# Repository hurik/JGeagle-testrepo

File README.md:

Check [visual-diffs-for-eagle-and-git](https://github.com/hurik/visual-diffs-for-eagle-and-git) for more information!

Using [9 Degrees of Freedom - Razor IMU](http://www.sparkfun.com/products/10736) and [Triple Axis Accelerometer & Gyro Breakout - MPU-6050](http://www.sparkfun.com/products/11028) eagle files from [SparkFun Electronics](http://www.sparkfun.com/).

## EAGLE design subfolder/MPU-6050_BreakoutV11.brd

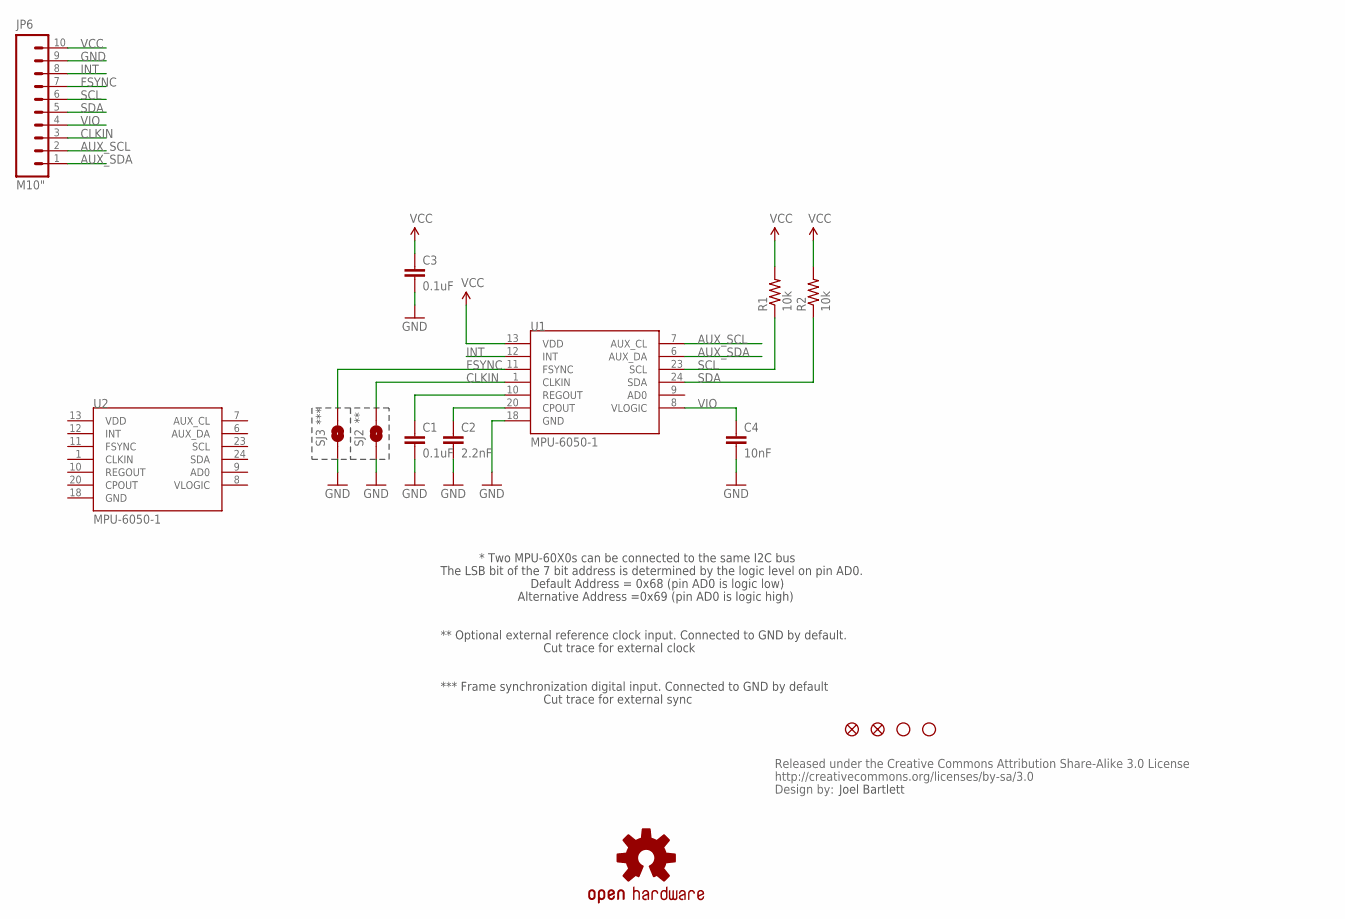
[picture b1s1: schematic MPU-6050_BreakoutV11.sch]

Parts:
C1, C3: 0.1uF; 0402-CAP
C2: 2.2nF; 0402-CAP
C4: 10nF; 0402-CAP
JP2, JP5: FIDUCIALUFIDUCIAL; MICRO-FIDUCIAL
JP3, JP4: STAND-OFFTIGHT; STAND-OFF-TIGHT
JP6: M10"; 1X10
R1, R2: 10k; 0402-RES
SJ2, SJ3: SOLDERJUMPERTRACE; SJ_2S-TRACE
U1, U2: MPU-6050-1; QFN-24-4MM2
U3: CREATIVE_COMMONS
U$1: OSHW-LOGOS; OSHW-LOGO-S

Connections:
AUX_SCL: JP6.2, U1.7 (AUX_CL)
AUX_SDA: JP6.1, U1.6 (AUX_DA)
CLKIN: JP6.3, SJ2.2, U1.1 (CLKIN)
FSYNC: JP6.7, SJ3.2, U1.11 (FSYNC)
GND: C1.2, C2.2, C3.2, C4.2, JP6.9, SJ2.1, SJ3.1, U1.18 (GND)
INT: JP6.8, U1.12 (INT)
unnamed: C2.1, U1.20 (CPOUT)
unnamed: C1.1, U1.10 (REGOUT)
SCL: JP6.6, R1.1, U1.23 (SCL)
SDA: JP6.5, R2.1, U1.24 (SDA)
VCC: C3.1, JP6.10, R1.2, R2.2, U1.13 (VDD)
VIO: C4.1, JP6.4, U1.8 (VLOGIC)

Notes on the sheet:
Joel Bartlett
*** Frame synchronization digital input. Connected to GND by default
***
Cut trace for external sync
* Two MPU-60X0s can be connected to the same I2C bus
Default Address = 0x68 (pin AD0 is logic low)
Alternative Address =0x69 (pin AD0 is logic high)
The LSB bit of the 7 bit address is determined by the logic level on pin AD0.
** Optional external reference clock input. Connected to GND by default.
Cut trace for external clock

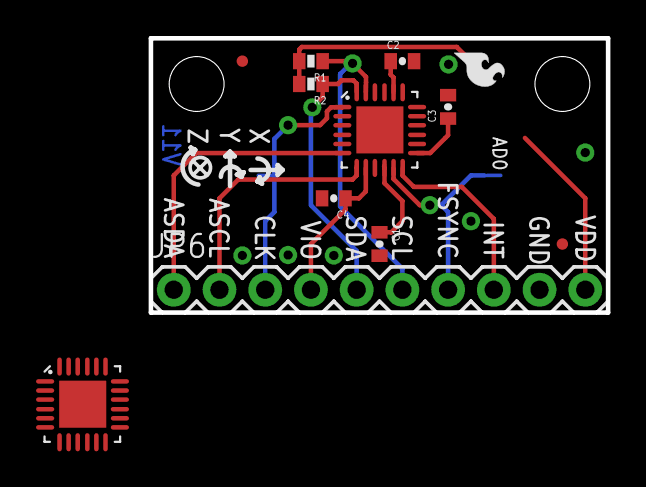
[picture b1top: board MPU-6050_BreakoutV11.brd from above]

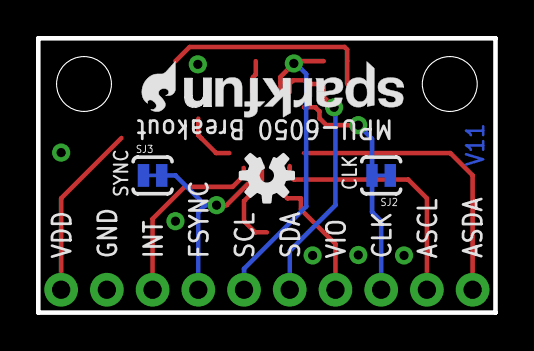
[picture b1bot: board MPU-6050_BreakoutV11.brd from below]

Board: 2 copper layers, 25.4 x 15.2 mm, 20 parts (5 on the bottom side), 12 nets.

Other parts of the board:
U$2, U$3: SFE-LOGO-FLAME
U$4: SFE-NEW-WEB

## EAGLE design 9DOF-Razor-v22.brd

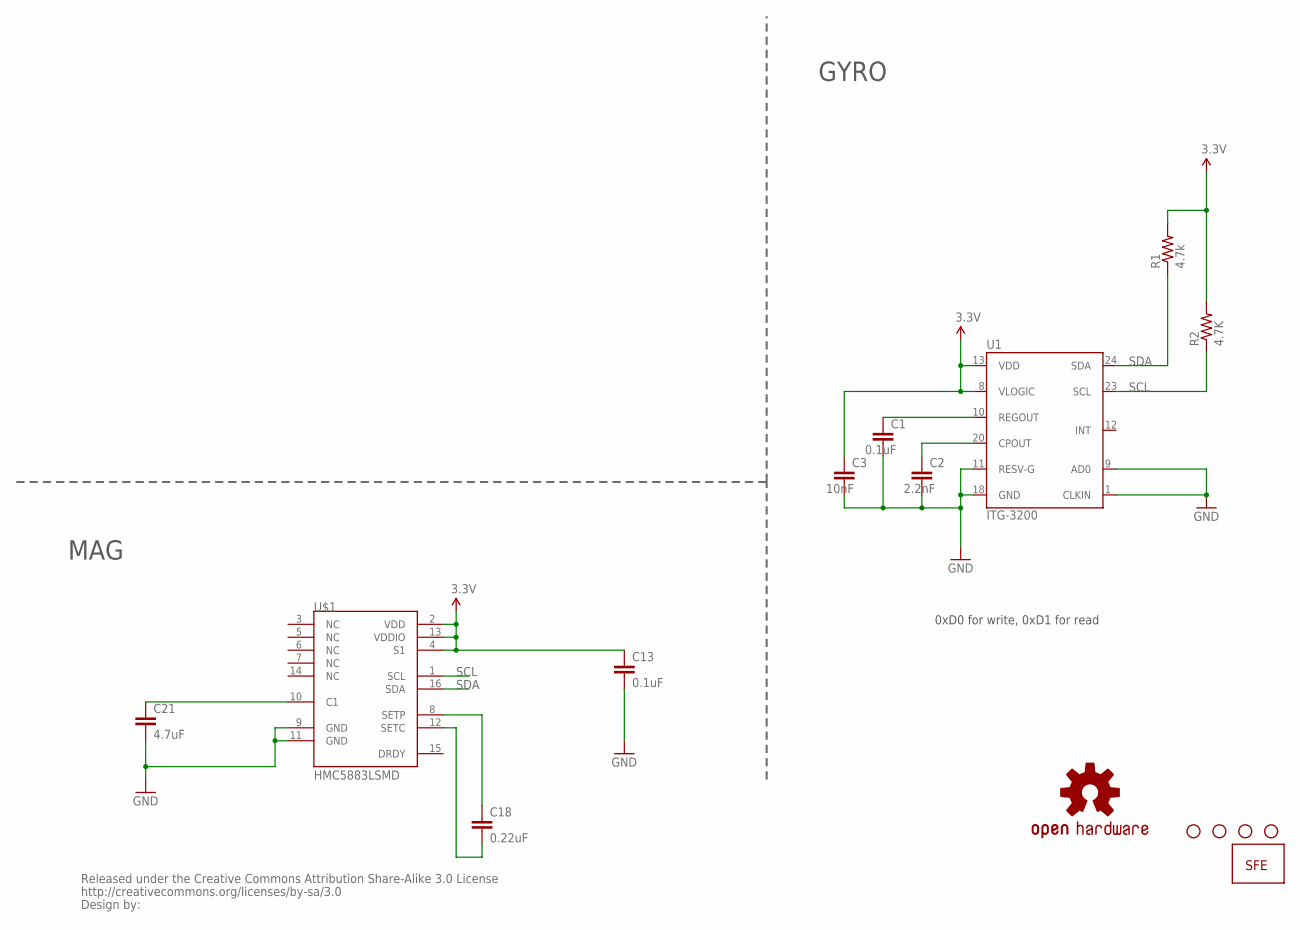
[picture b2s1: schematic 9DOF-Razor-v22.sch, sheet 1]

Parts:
C1, C13: 0.1uF; 0402-CAP
C2: 2.2nF; 0402-CAP
C3: 10nF; 0402-CAP
C18: 0.22uF; 0402-CAP
C21: 4.7uF; 0402-CAP
JP2, JP4, JP5, JP6: STAND-OFF
JP3: LOGO-SFENEW; SFE-NEW-WEBLOGO
R1: 4.7k; 0402-RES
R2: 4.7K; 0402-RES
U1: ITG-3200; QFN-24
U$1: HMC5883LSMD; 16LPCC
U$2: CREATIVE_COMMONS
U$4: OSHW-LOGOL; OSHW-LOGO-L

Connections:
3.3V: C3.1, C13.1, R1.2, R2.2, U1.8 (VLOGIC), U1.13 (VDD), U$1.2 (VDD), U$1.4 (S1), U$1.13 (VDDIO); also elsewhere on the board
GND: C1.2, C2.2, C3.2, C13.2, C21.2, U1.1 (CLKIN), U1.9 (AD0), U1.11 (RESV-G), U1.18 (GND), U$1.9 (GND), U$1.11 (GND); also elsewhere on the board
unnamed: C18.2, U$1.8 (SETP)
unnamed: C18.1, U$1.12 (SETC)
unnamed: C1.1, U1.10 (REGOUT)
unnamed: C2.1, U1.20 (CPOUT)
unnamed: C21.1, U$1.10 (C1)
SCL: R2.1, U1.23 (SCL), U$1.1 (SCL); also elsewhere on the board
SDA: R1.1, U1.24 (SDA), U$1.16 (SDA); also elsewhere on the board

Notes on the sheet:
GYRO
MAG
0xD0 for write, 0xD1 for read

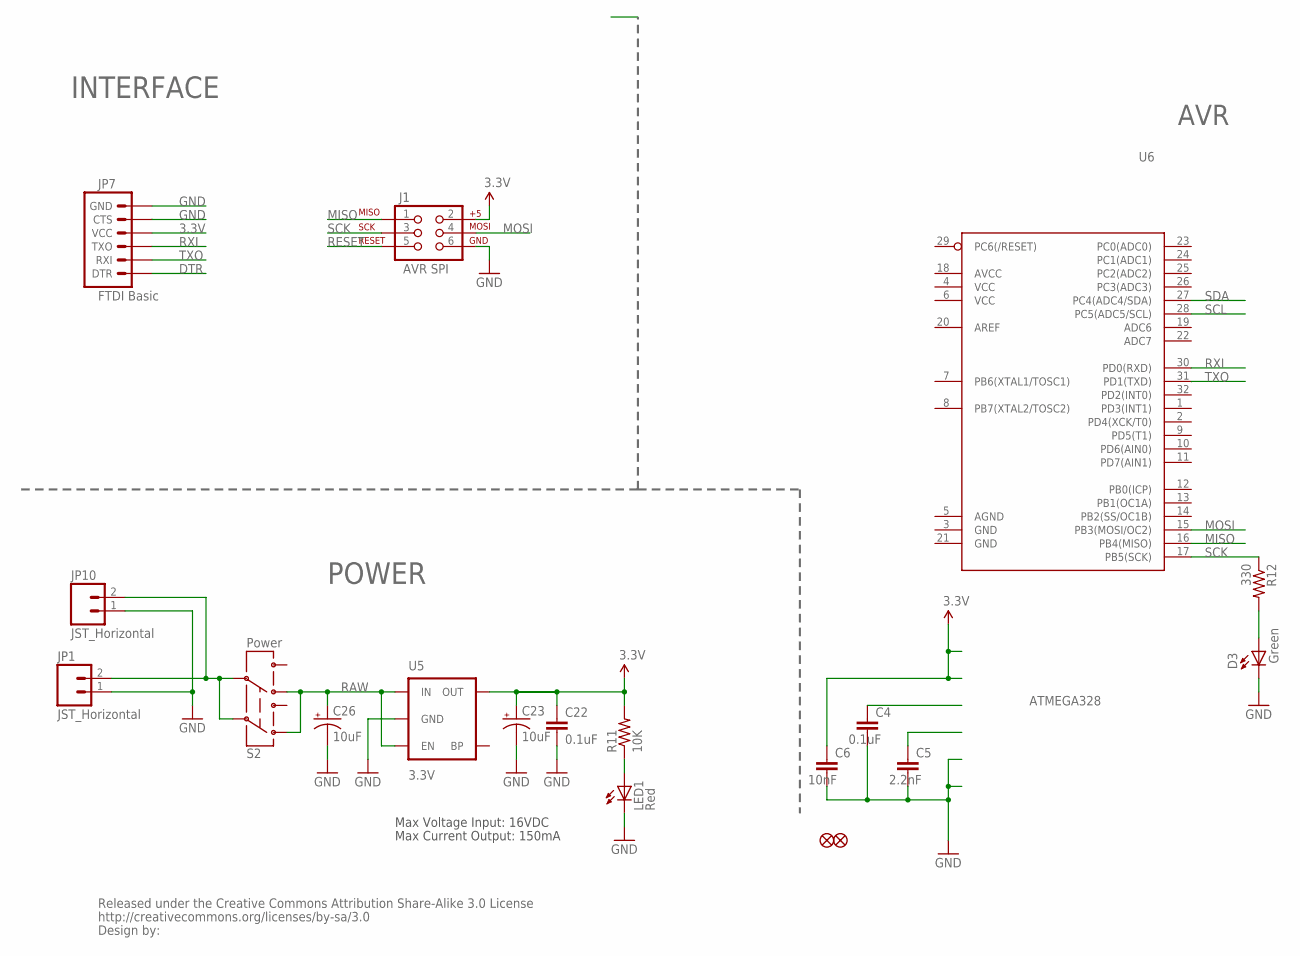
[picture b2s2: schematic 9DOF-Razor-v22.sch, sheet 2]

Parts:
C4, C22: 0.1uF; 0402-CAP
C5: 2.2nF; 0402-CAP
C6: 10nF; 0402-CAP
C23, C26: 10uF; EIA3216
D3: Green; LED-0603
J1: AVR_SPI_PRG_6PTH; 2X3
JP1: JST_Horizontal; JST-2-SMD
JP7: FTDI Basic; 1X06
JP10: JST_Horizontal; 1X02
JP11, JP12: FIDUCIAL1X2.5; FIDUCIAL-1X2.5
LED1: Red; LED-0603
R11: 10K; 0402-RES
R12: 330; 0402-RES
S2: Power; AYZ0202
U5: 3.3V; SOT23-5
U6: ATMEGA328; TQFP32-08
U$3: CREATIVE_COMMONS

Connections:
3.3V: C6.1, C22.1, C23.A (+), J1.2, JP7.4 (VCC), R11.2, U5.5 (OUT); also elsewhere on the board
DTR: JP7.1 (DTR)
GND: C4.2, C5.2, C6.2, C22.2, C23.C (-), C26.C (-), D3.C, J1.6, JP1.1, JP7.5 (CTS), JP7.6 (GND), JP10.1, LED1.C, U5.2 (GND); also elsewhere on the board
MISO: J1.1, U6.16 (PB4(MISO))
MOSI: J1.4, U6.15 (PB3(MOSI/OC2))
unnamed: D3.A, R12.2
unnamed: JP1.2, JP10.2, S2.2, S2.5
unnamed: LED1.A, R11.1
RAW: C26.A (+), S2.1, S2.4, U5.1 (IN), U5.3 (EN)
RESET: J1.5
RXI: JP7.3 (TXO), U6.30 (PD0(RXD))
SCK: J1.3, R12.1, U6.17 (PB5(SCK))
SCL: U6.28 (PC5(ADC5/SCL)); also elsewhere on the board
SDA: U6.27 (PC4(ADC4/SDA)); also elsewhere on the board
TXO: JP7.2 (RXI), U6.31 (PD1(TXD))

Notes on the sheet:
Max Voltage Input: 16VDC
Max Current Output: 150mA
AVR
INTERFACE
POWER
AVR SPI

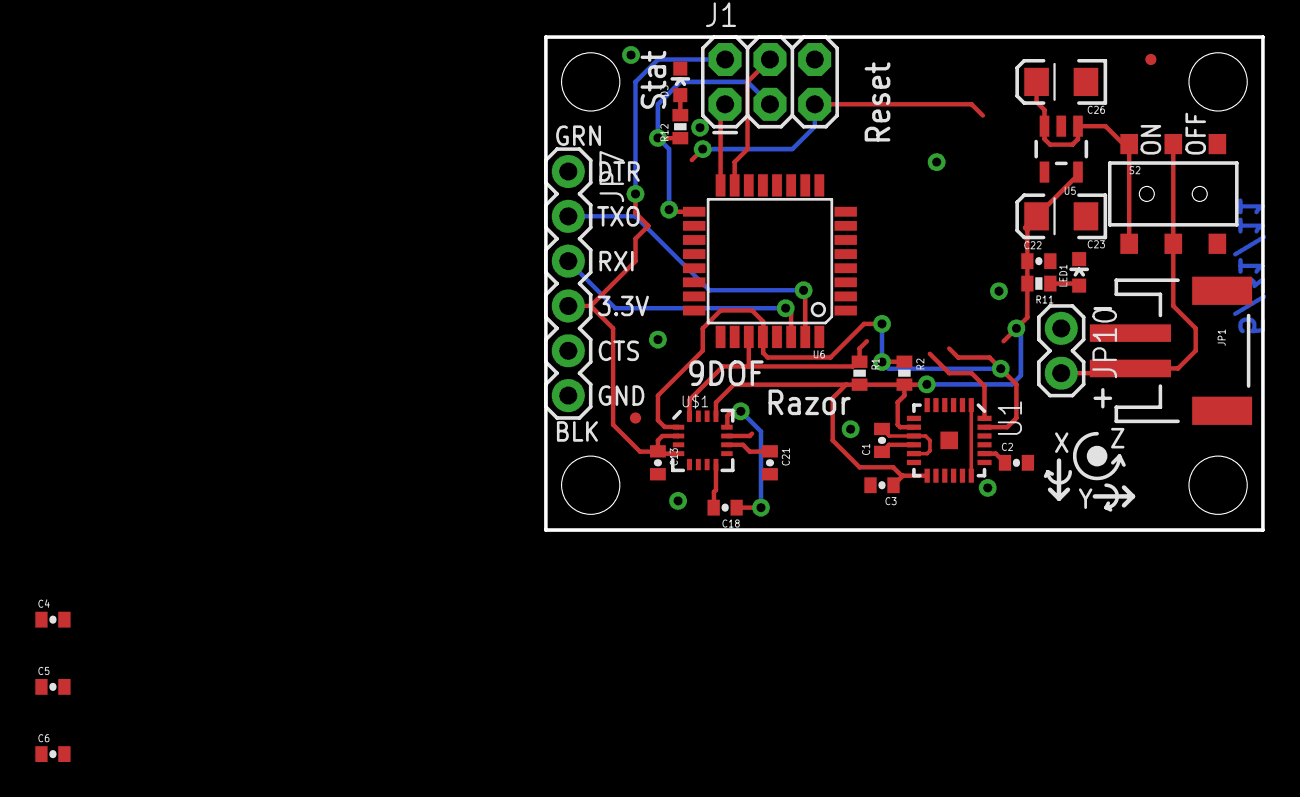
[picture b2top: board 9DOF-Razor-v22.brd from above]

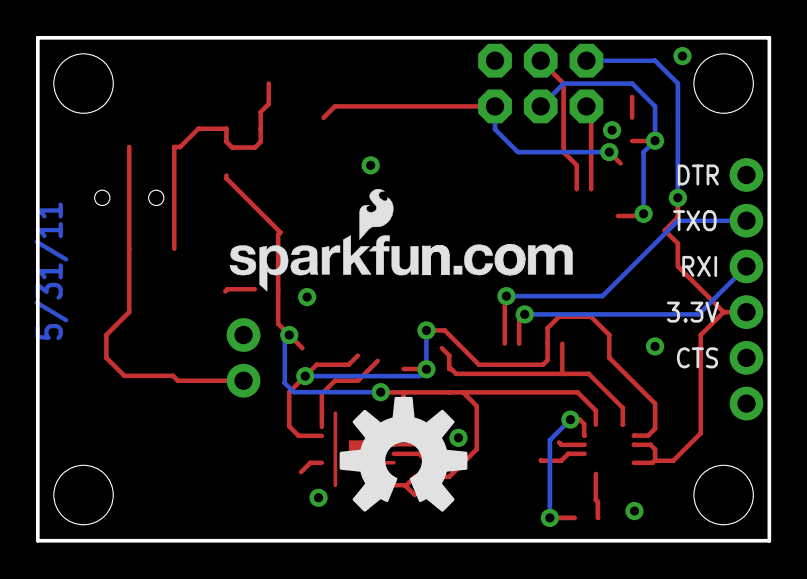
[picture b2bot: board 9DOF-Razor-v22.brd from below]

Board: 2 copper layers, 40.6 x 27.9 mm, 37 parts (2 on the bottom side), 18 nets.

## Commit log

2012-06-13 added gyro and interface
2012-06-13 deleted accel
2012-06-13 a lot of small changes on the schematic
2012-06-13 movement, adding and erasing elements on schematic page 2
2012-06-13 added readme
2012-06-14 added files in a subfolder
2012-06-15 changed files in subfolder
2012-06-17 folder in folder and same filename
2012-06-17 changes in the subfolder

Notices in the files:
parts and their libraries:
SparkFun: Released under the Creative Commons Attribution Share-Alike 3.0 License
SparkFun: http://creativecommons.org/licenses/by-sa/3.0
